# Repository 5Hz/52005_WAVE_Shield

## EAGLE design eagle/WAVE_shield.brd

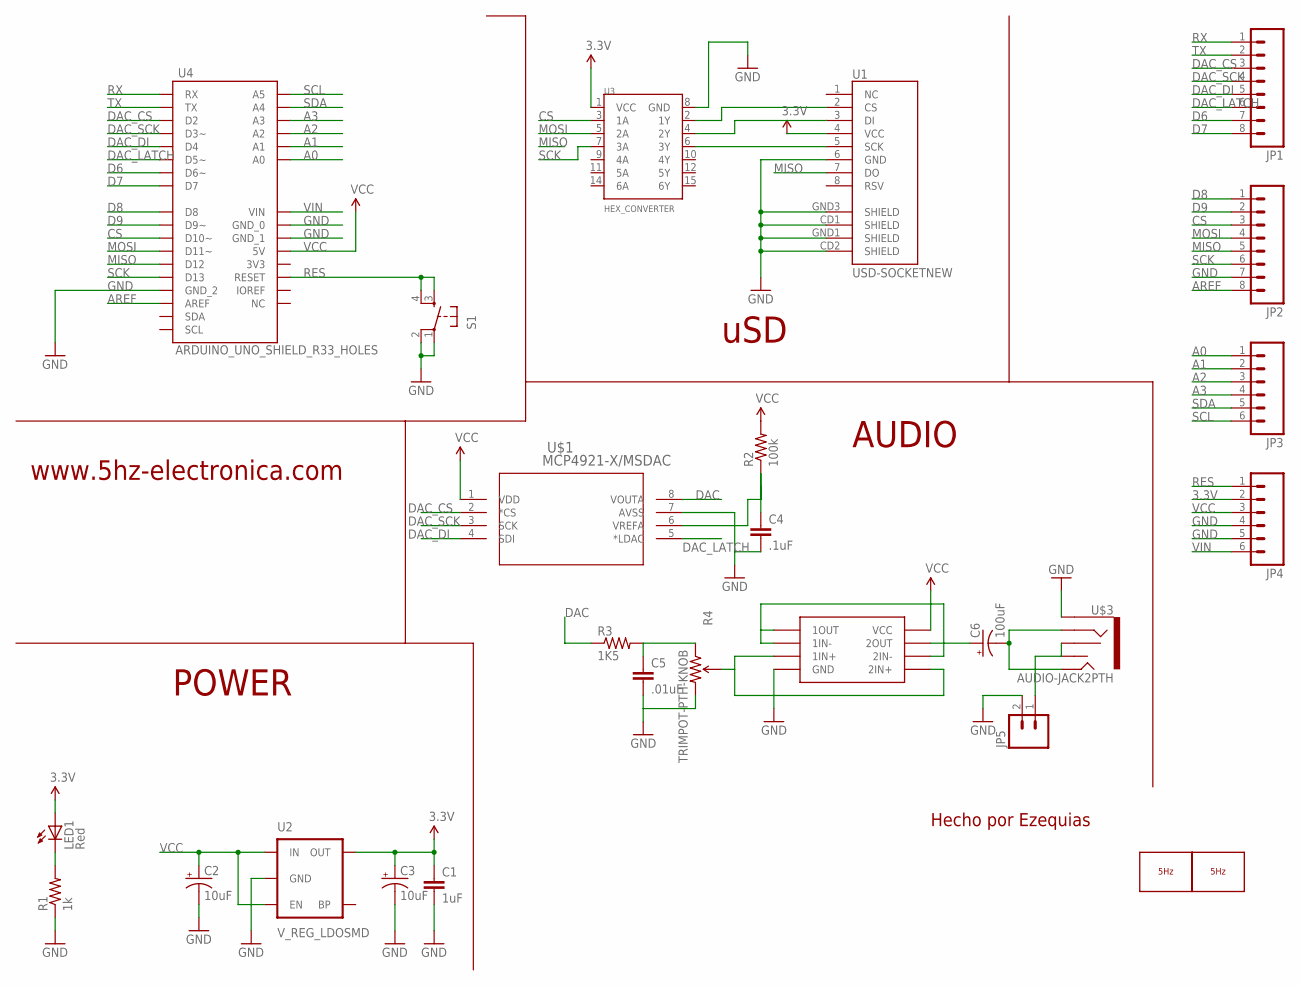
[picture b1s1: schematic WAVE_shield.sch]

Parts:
C1: 1uF; 0603-CAP
C2, C3: 10uF; EIA3216
C4: .1uF; 0603-CAP
C5: .01uF; 0603-CAP
C6: 100uF; EIA3216
JP1, JP2: M08; 1X08
JP3, JP4: M06SIP; 1X06
JP5: M02PTH; 1X02
LED1: Red; LED-0603
LOGO2: LOGO_5HZ_MAIN_10MM; 5HZ_LOGO_MAIN_10MM
LOGO3: LOGO_5HZ_H_COOPER_15MM; 5HZ_LOGO_H_COOPER_15MM
R1: 1k; 0603-RES
R2: 100k; 0603-RES
R3: 1K5; 0603-RES
R4: TRIMPOT-PTH-KNOB; 3386U
S1: TAC_SWITCHSMD; TACTILE_SWITCH_SMD
U1: USD-SOCKETNEW; MICRO-SD-SOCKET-PP
U2: V_REG_LDOSMD; SOT23-5
U3: HEX_CONVERTER; SO016
U4: ARDUINO_UNO_SHIELD_R33_HOLES; UNO_R3_SHIELD_3_HOLES_NO_SILK
U$1: MCP4921-X/MSDAC; MSOP8_MC
U$2: LM2904DGKROPAMP; MSOP8
U$3: AUDIO-JACK2PTH; AUDIO-JACK

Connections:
3.3V: C1.1, C3.A (+), JP4.2, LED1.A, U1.4 (VCC), U2.5 (OUT), U3.1 (VCC)
A0: JP3.1, U4.A0
A1: JP3.2, U4.A1
A2: JP3.3, U4.A2
A3: JP3.4, U4.A3
AREF: JP2.8, U4.AREF
CS: JP2.3, U3.3 (1A), U4.D10 (D10~)
D6: JP1.7, U4.D6 (D6~)
D7: JP1.8, U4.D7
D8: JP2.1, U4.D8
D9: JP2.2, U4.D9 (D9~)
DAC: R3.1, U$1.8 (VOUTA)
DAC_CS: JP1.3, U4.D2, U$1.2 (*CS)
DAC_DI: JP1.5, U4.D4, U$1.4 (SDI)
DAC_LATCH: JP1.6, U4.D5 (D5~), U$1.5 (*LDAC)
DAC_SCK: JP1.4, U4.D3 (D3~), U$1.3 (SCK)
GND: C1.2, C2.C (-), C3.C (-), C4.2, C5.2, JP2.7, JP4.4, JP4.5, JP5.2, R1.1, R4.3 (CW), S1.1, S1.2, U1.6 (GND), U1.CD1 (SHIELD), U1.CD2 (SHIELD), U1.GND1 (SHIELD), U1.GND3 (SHIELD), U2.2 (GND), U3.8 (GND), U4.GND_0, U4.GND_1, U4.GND_2, U$1.7 (AVSS), U$2.4 (GND), U$3.SLEEVE
MISO: JP2.5, U1.7 (DO), U4.D12
MOSI: JP2.4, U3.5 (2A), U4.D11 (D11~)
unnamed: C5.1, R3.2, R4.1 (CCW)
unnamed: U1.3 (DI), U3.4 (2Y)
unnamed: U1.5 (SCK), U3.6 (3Y)
unnamed: LED1.C, R1.2
unnamed: U1.2 (CS), U3.2 (1Y)
unnamed: R4.2 (WIPER), U$2.3 (1IN+), U$2.5 (2IN+)
unnamed: C4.1, R2.1, U$1.6 (VREFA)
unnamed: C6.A (+), U$2.1 (1OUT), U$2.2 (1IN-), U$2.6 (2IN-), U$2.7 (2OUT)
unnamed: C6.C (-), U$3.RING, U$3.TIP
unnamed: JP5.1, U$3.RSH, U$3.TSH
RES: JP4.1, S1.3, S1.4, U4.RES (RESET)
RX: JP1.1, U4.RX
SCK: JP2.6, U3.7 (3A), U4.D13
SCL: JP3.6, U4.A5
SDA: JP3.5, U4.A4
TX: JP1.2, U4.TX
VCC: C2.A (+), JP4.3, R2.2, U2.1 (IN), U2.3 (EN), U4.5V, U$1.1 (VDD), U$2.8 (VCC)
VIN: JP4.6, U4.VIN

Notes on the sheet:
POWER
uSD
AUDIO
Hecho por Ezequias
www.5hz-electronica.com

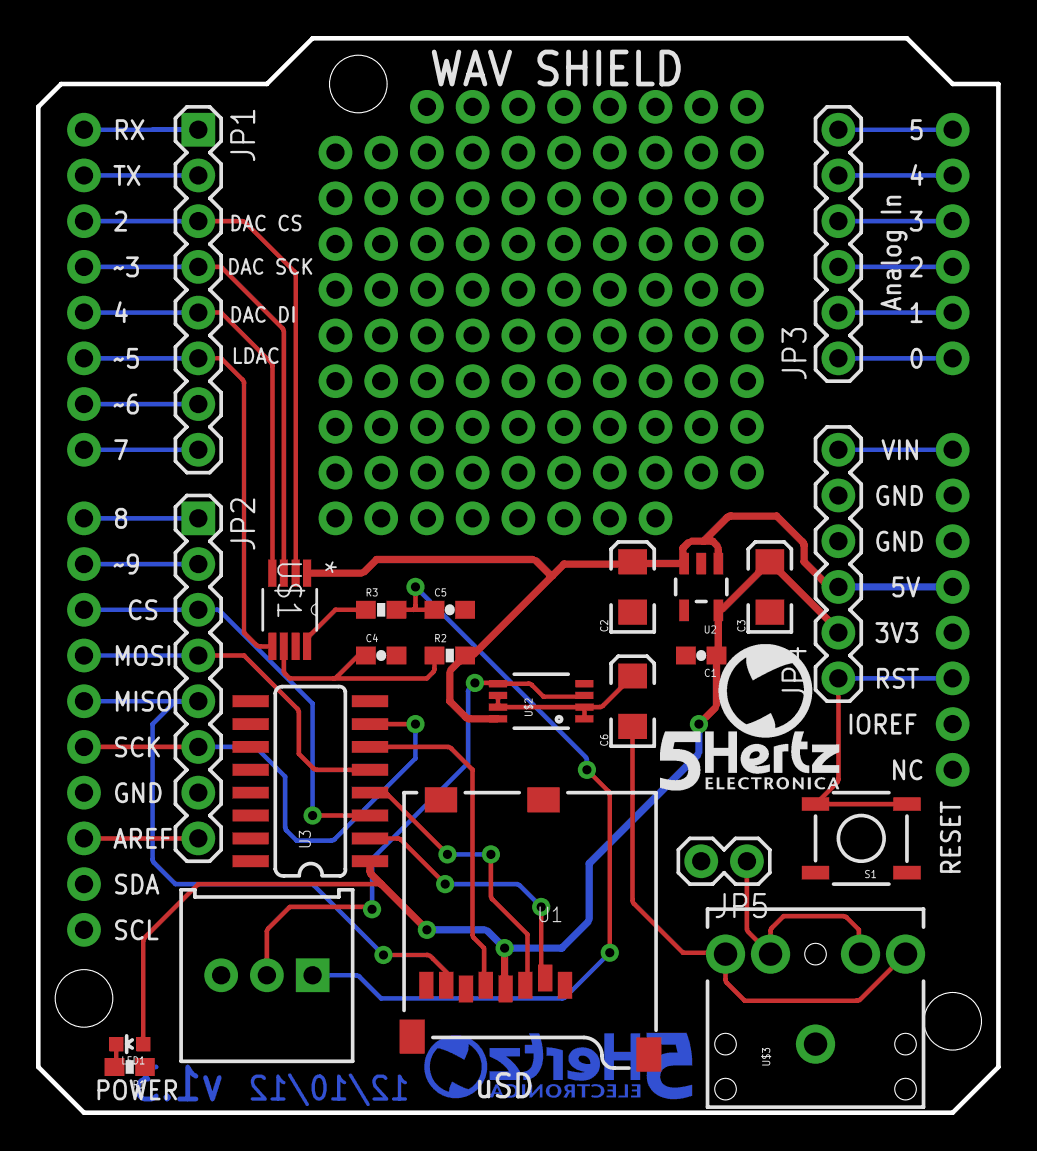
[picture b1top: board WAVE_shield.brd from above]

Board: 2 copper layers, 53.3 x 59.7 mm, 26 parts (1 on the bottom side), 37 nets.

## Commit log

2014-01-09 creacion
